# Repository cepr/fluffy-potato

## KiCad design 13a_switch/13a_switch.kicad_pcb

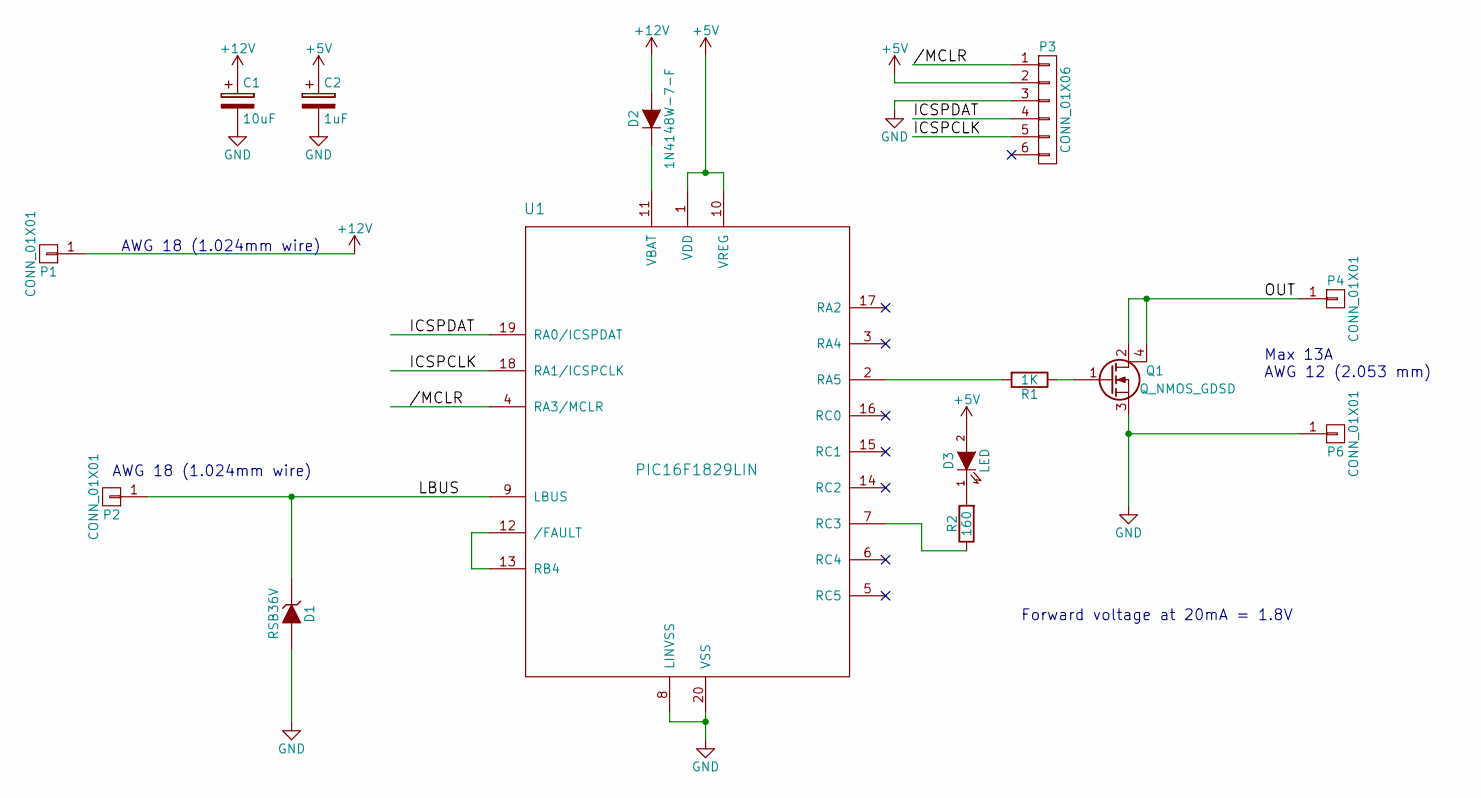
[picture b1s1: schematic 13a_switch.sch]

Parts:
C1: 10uF; C_1210_HandSoldering; DIGIKEY 445-13057-1-ND
C2: 1uF; C_0805_HandSoldering; DIGIKEY 490-8046-1-ND
D1: RSB36V; SOD-323_HandSoldering; DIGIKEY RSB36VTE-17CT-ND
D2: 1N4148W-7-F; SOD-123; DIGIKEY 1N4148W-FDICT-ND
D3: LED; LED_0805; DIGIKEY 475-1415-1-ND
P1, P2, P4, P6: CONN_01X01; 1pin
P3: CONN_01X06; Pin_Header_Straight_1x06
Q1: Q_NMOS_GDSD; SOT-223; DIGIKEY 497-14326-1-ND
R1: 1K; R_0805_HandSoldering; DIGIKEY 311-1.00KCRCT-ND
R2: 160; R_0805_HandSoldering; DIGIKEY 311-160CRCT-ND
U1: PIC16F1829LIN; SSOP-20; DIGIKEY PIC16F1829LIN-I/SS-ND

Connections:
+5V: C2.1, D3.2 (A), P3.2, U1.1 (VDD), U1.10 (VREG)
+12V: C1.1, D2.2 (A), P1.1
//MCLR: P3.1, U1.4 (RA3/MCLR)
/ICSPCLK: P3.5, U1.18 (RA1/ICSPCLK)
/ICSPDAT: P3.4, U1.19 (RA0/ICSPDAT)
/LBUS: D1.1 (K), P2.1, U1.9 (LBUS)
/OUT: P4.1, Q1.2 (D), Q1.4 (D)
GND: C1.2, C2.2, D1.2 (A), P3.3, P6.1, Q1.3 (S), U1.8 (LINVSS), U1.20 (VSS)
unnamed: D2.1 (K), U1.11 (VBAT)
unnamed: D3.1 (K), R2.2
unnamed: Q1.1 (G), R1.1
unnamed: R1.2, U1.2 (RA5)
unnamed: R2.1, U1.7 (RC3)
unnamed: U1.12 (/FAULT), U1.13 (RB4)

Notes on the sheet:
Max 13A AWG 12 (2.053 mm)
AWG 18 (1.024mm wire)
Forward voltage at 20mA = 1.8V

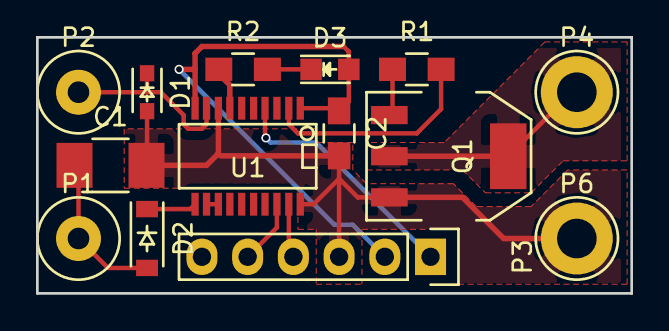
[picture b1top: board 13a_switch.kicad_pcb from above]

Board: 2 copper layers, 33.0 x 14.2 mm, 14 parts (0 on the bottom side), 14 nets.

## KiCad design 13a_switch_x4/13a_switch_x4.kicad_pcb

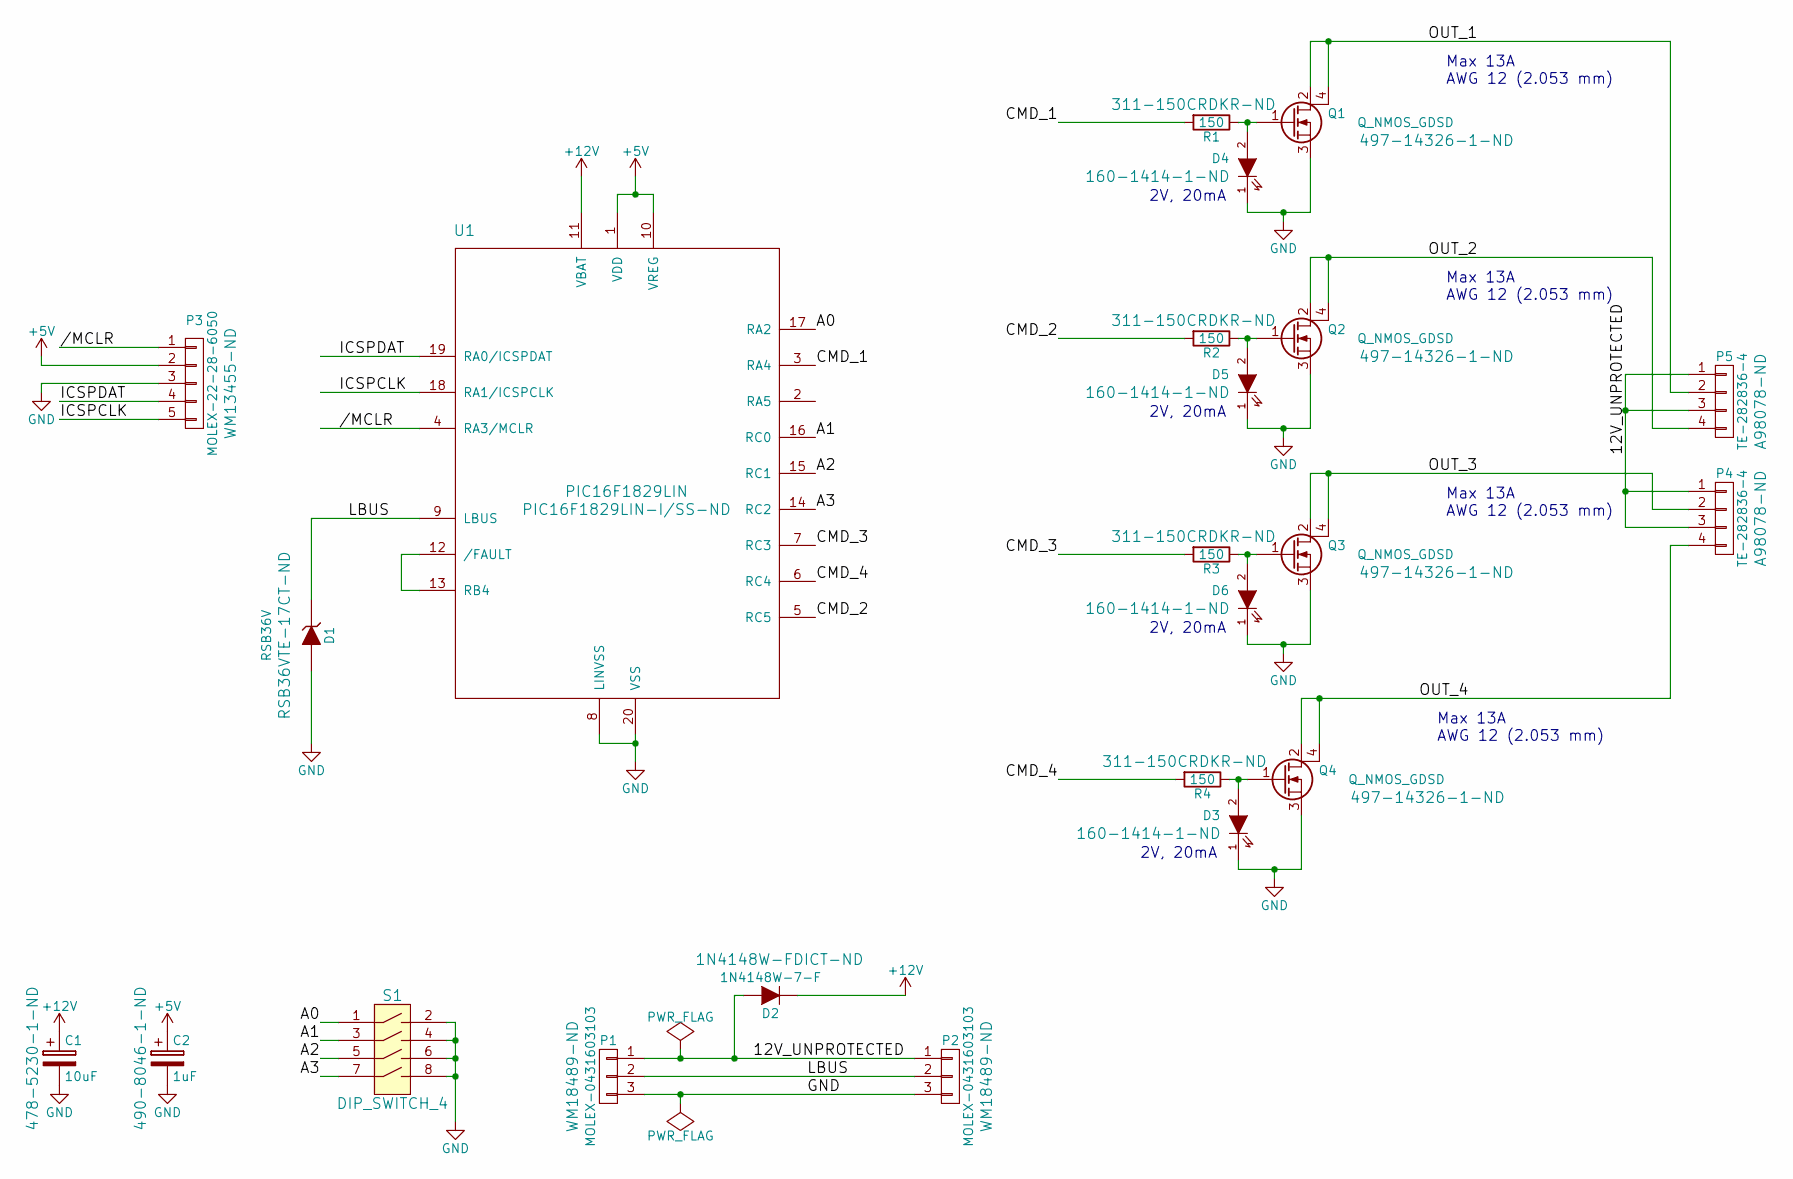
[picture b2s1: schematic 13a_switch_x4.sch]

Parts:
C1: 10uF; C_1210_HandSoldering; DIGIKEY 478-5230-1-ND
C2: 1uF; C_0805_HandSoldering; DIGIKEY 490-8046-1-ND
D1: RSB36V; SOD-323_HandSoldering; DIGIKEY RSB36VTE-17CT-ND
D2: 1N4148W-7-F; SOD-123; DIGIKEY 1N4148W-FDICT-ND
D3, D4, D5, D6: LITEON-LTST-C170KGKT; LED_0805; DIGIKEY 160-1414-1-ND
P1, P2: MOLEX-0431603103; Molex_Sabre_43160-XX03_03x7.49mm_Angled_BoardLock; DIGIKEY WM18489-ND
P3: MOLEX-22-28-6050; Pin_Header_Straight_1x05; DIGIKEY WM13455-ND
P4, P5: TE-282836-4; bornier4; DIGIKEY A98078-ND
Q1, Q2, Q3, Q4: Q_NMOS_GDSD; SOT-223; DIGIKEY 497-14326-1-ND
R1, R2, R3, R4: 150; R_0805_HandSoldering; DIGIKEY 311-150CRDKR-ND
S1: DIP_SWITCH_4; Copal_CHS-04TB; DIGIKEY 563-1008-1-ND
U1: PIC16F1829LIN; SSOP-20_5.3x7.2mm_Pitch0.65mm; DIGIKEY PIC16F1829LIN-I/SS-ND

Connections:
+5V: C2.1, P3.2, U1.1 (VDD), U1.10 (VREG)
+12V: C1.1, D2.1 (K), U1.11 (VBAT)
/12V_UNPROTECTED: D2.2 (A), P1.1, P2.1, P4.1, P4.3, P5.1, P5.3
//MCLR: P3.1, U1.4 (RA3/MCLR)
/A0: S1.1, U1.17 (RA2)
/A1: S1.3, U1.16 (RC0)
/A2: S1.5, U1.15 (RC1)
/A3: S1.7, U1.14 (RC2)
/CMD_1: R1.2, U1.3 (RA4)
/CMD_2: R2.2, U1.5 (RC5)
/CMD_3: R3.2, U1.7 (RC3)
/CMD_4: R4.2, U1.6 (RC4)
/ICSPCLK: P3.5, U1.18 (RA1/ICSPCLK)
/ICSPDAT: P3.4, U1.19 (RA0/ICSPDAT)
/LBUS: D1.1 (K), P1.2, P2.2, U1.9 (LBUS)
/OUT_1: P5.2, Q1.2 (D), Q1.4 (D)
/OUT_2: P5.4, Q2.2 (D), Q2.4 (D)
/OUT_3: P4.2, Q3.2 (D), Q3.4 (D)
/OUT_4: P4.4, Q4.2 (D), Q4.4 (D)
GND: C1.2, C2.2, D1.2 (A), D3.1 (K), D4.1 (K), D5.1 (K), D6.1 (K), P1.3, P2.3, P3.3, Q1.3 (S), Q2.3 (S), Q3.3 (S), Q4.3 (S), S1.2, S1.4, S1.6, S1.8, U1.8 (LINVSS), U1.20 (VSS)
unnamed: D3.2 (A), Q4.1 (G), R4.1
unnamed: D4.2 (A), Q1.1 (G), R1.1
unnamed: D5.2 (A), Q2.1 (G), R2.1
unnamed: D6.2 (A), Q3.1 (G), R3.1
unnamed: U1.12 (/FAULT), U1.13 (RB4)

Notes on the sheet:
Max 13A AWG 12 (2.053 mm)
2V, 20mA

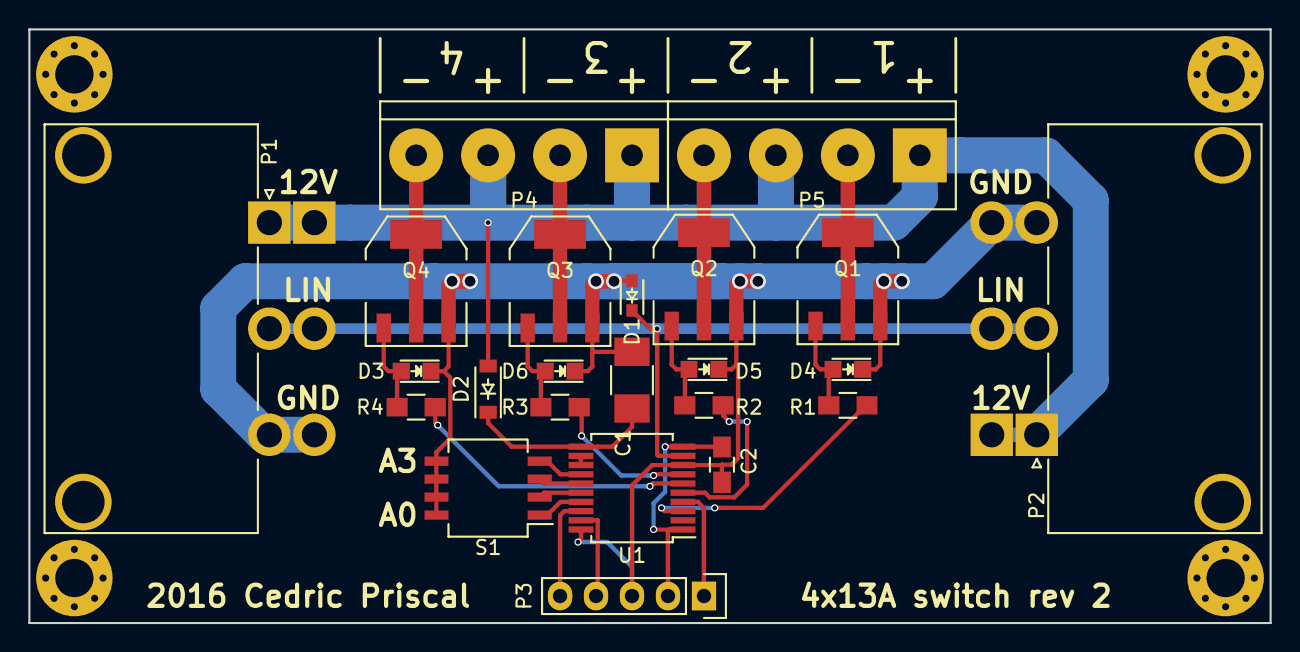
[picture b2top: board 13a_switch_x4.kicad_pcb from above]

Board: 2 copper layers, 87.6 x 41.9 mm, 23 parts (0 on the bottom side), 25 nets.

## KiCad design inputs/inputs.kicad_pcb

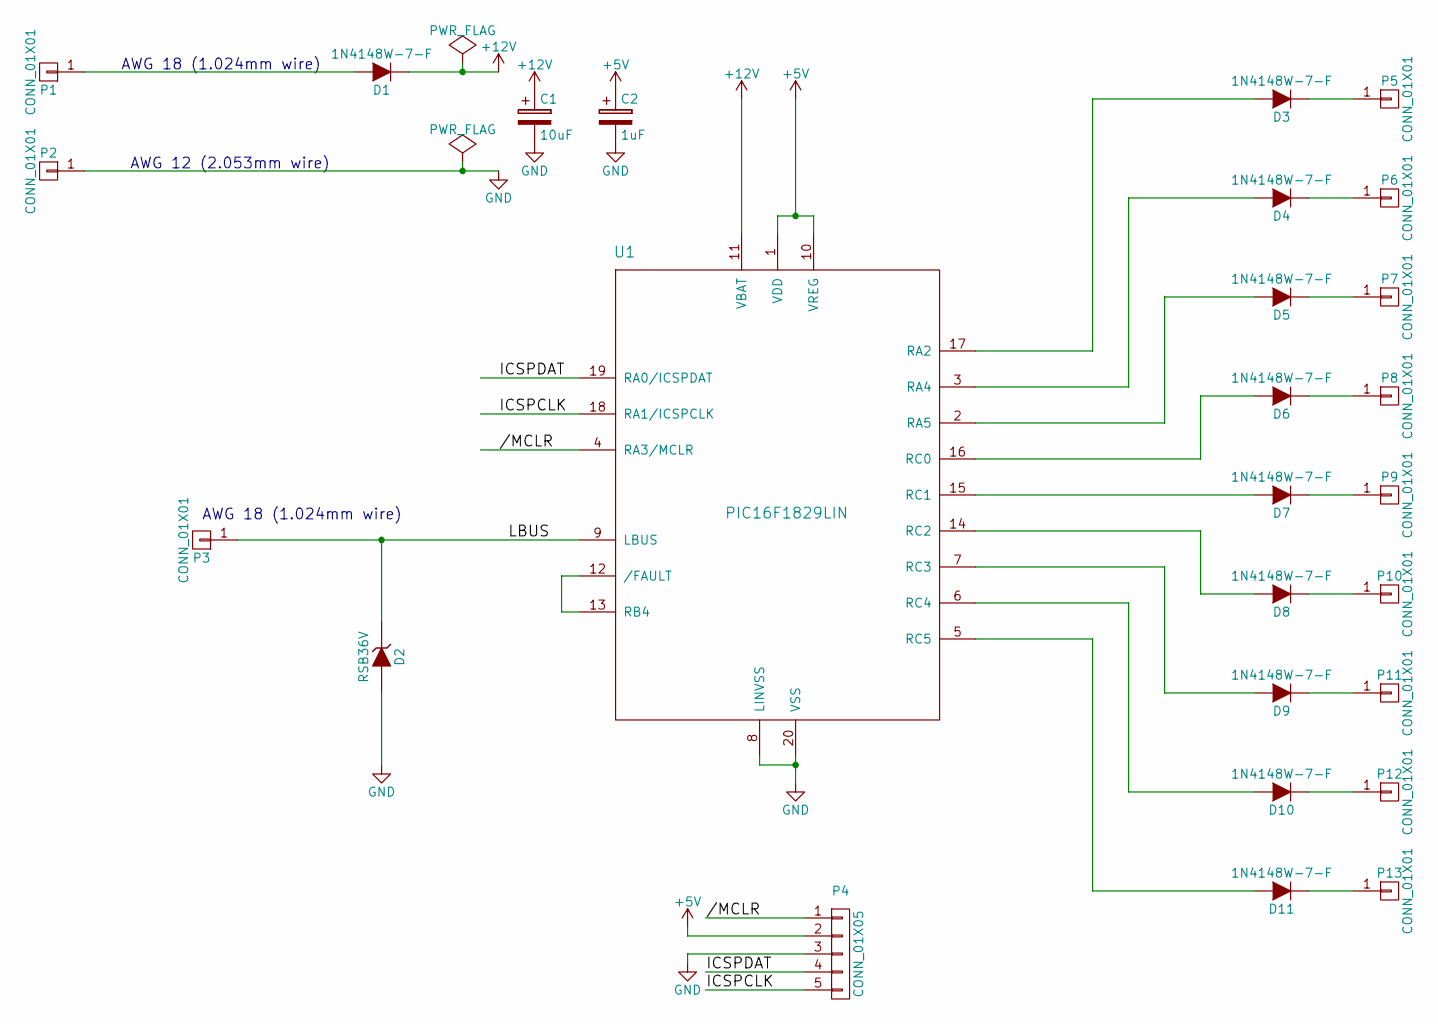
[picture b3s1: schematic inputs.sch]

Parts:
C1: 10uF; C_1210_HandSoldering; DIGIKEY 445-13057-1-ND
C2: 1uF; C_0805_HandSoldering; DIGIKEY 490-8046-1-ND
D1, D3, D4, D5, D6, D7, D8, D9, D10, D11: 1N4148W-7-F; SOD-123; DIGIKEY 1N4148W-FDICT-ND
D2: RSB36V; SOD-323_HandSoldering; DIGIKEY RSB36VTE-17CT-ND
P1, P2, P3, P5, P6, P7, P8, P9, P10, P11, P12, P13: CONN_01X01; wire_awg_18
P4: CONN_01X05; Pin_Header_Angled_1x05
U1: PIC16F1829LIN; SSOP-20_5.3x7.2mm_Pitch0.65mm; DIGIKEY PIC16F1829LIN-I/SS-ND

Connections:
+5V: C2.1, P4.2, U1.1 (VDD), U1.10 (VREG)
+12V: C1.1, D1.1 (K), U1.11 (VBAT)
//MCLR: P4.1, U1.4 (RA3/MCLR)
/ICSPCLK: P4.5, U1.18 (RA1/ICSPCLK)
/ICSPDAT: P4.4, U1.19 (RA0/ICSPDAT)
/LBUS: D2.1 (K), P3.1, U1.9 (LBUS)
GND: C1.2, C2.2, D2.2 (A), P2.1, P4.3, U1.8 (LINVSS), U1.20 (VSS)
unnamed: D1.2 (A), P1.1
unnamed: D3.1 (K), P5.1
unnamed: D3.2 (A), U1.17 (RA2)
unnamed: D4.1 (K), P6.1
unnamed: D4.2 (A), U1.3 (RA4)
unnamed: D5.1 (K), P7.1
unnamed: D5.2 (A), U1.2 (RA5)
unnamed: D6.1 (K), P8.1
unnamed: D6.2 (A), U1.16 (RC0)
unnamed: D7.1 (K), P9.1
unnamed: D7.2 (A), U1.15 (RC1)
unnamed: D8.1 (K), P10.1
unnamed: D8.2 (A), U1.14 (RC2)
unnamed: D9.1 (K), P11.1
unnamed: D9.2 (A), U1.7 (RC3)
unnamed: D10.1 (K), P12.1
unnamed: D10.2 (A), U1.6 (RC4)
unnamed: D11.1 (K), P13.1
unnamed: D11.2 (A), U1.5 (RC5)
unnamed: U1.12 (/FAULT), U1.13 (RB4)

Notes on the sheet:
AWG 18 (1.024mm wire)
AWG 12 (2.053mm wire)

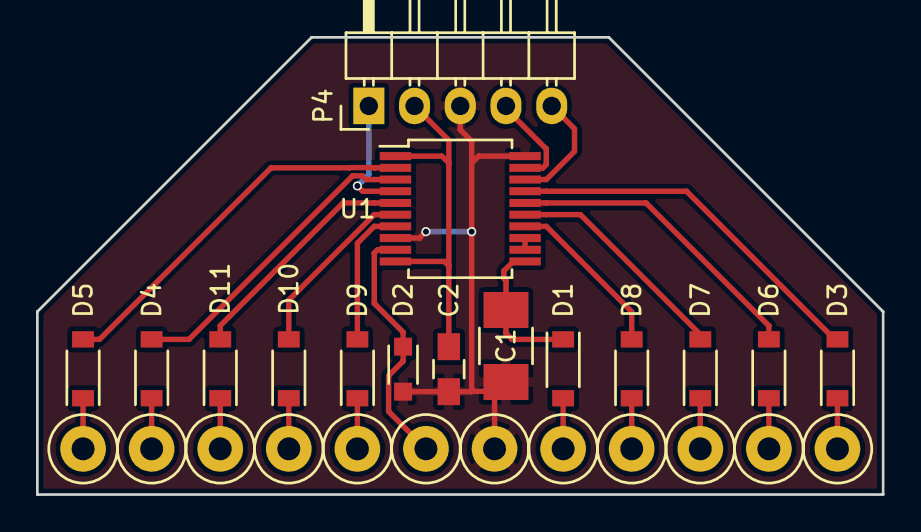
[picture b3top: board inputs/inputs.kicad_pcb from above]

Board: 2 copper layers, 47.0 x 25.4 mm, 27 parts (0 on the bottom side), 27 nets.

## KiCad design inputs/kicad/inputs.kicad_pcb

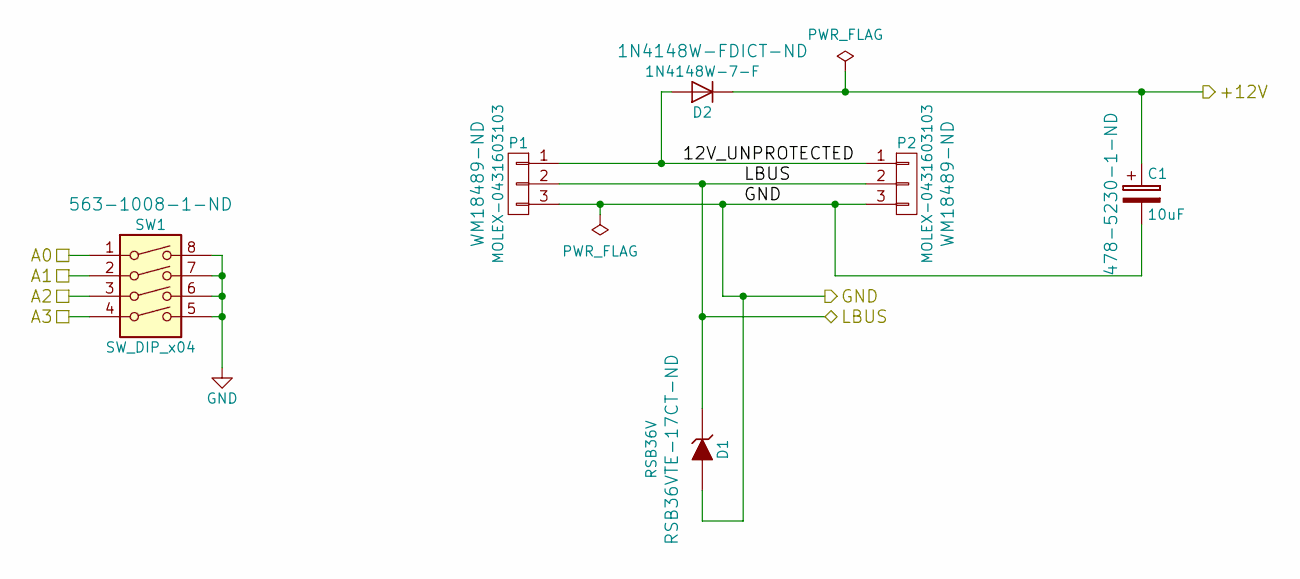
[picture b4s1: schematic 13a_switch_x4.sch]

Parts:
C1: 10uF; C_1210_HandSoldering; DIGIKEY 478-5230-1-ND
D1: RSB36V; SOD-323_HandSoldering; DIGIKEY RSB36VTE-17CT-ND
D2: 1N4148W-7-F; SOD-123; DIGIKEY 1N4148W-FDICT-ND
P1, P2: MOLEX-0431603103; Molex_Sabre_43160-XX03_03x7.49mm_Angled_BoardLock; DIGIKEY WM18489-ND
SW1: SW_DIP_x04; SW_DIP_x4_W7.62mm_Slide_Copal_CHS-B; DIGIKEY 563-1008-1-ND

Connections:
/Sheet584DA639/+12V: C1.1, D2.1 (K); also elsewhere on the board
/Sheet584DA639/LBUS: D1.1 (K), P1.2, P2.2; also elsewhere on the board
/lin_common/12V_UNPROTECTED: D2.2 (A), P1.1, P2.1
/lin_common/A0: SW1.1; also elsewhere on the board
/lin_common/A1: SW1.2; also elsewhere on the board
/lin_common/A2: SW1.3; also elsewhere on the board
/lin_common/A3: SW1.4; also elsewhere on the board
GND: C1.2, D1.2 (A), P1.3, P2.3, SW1.5, SW1.6, SW1.7, SW1.8; also elsewhere on the board

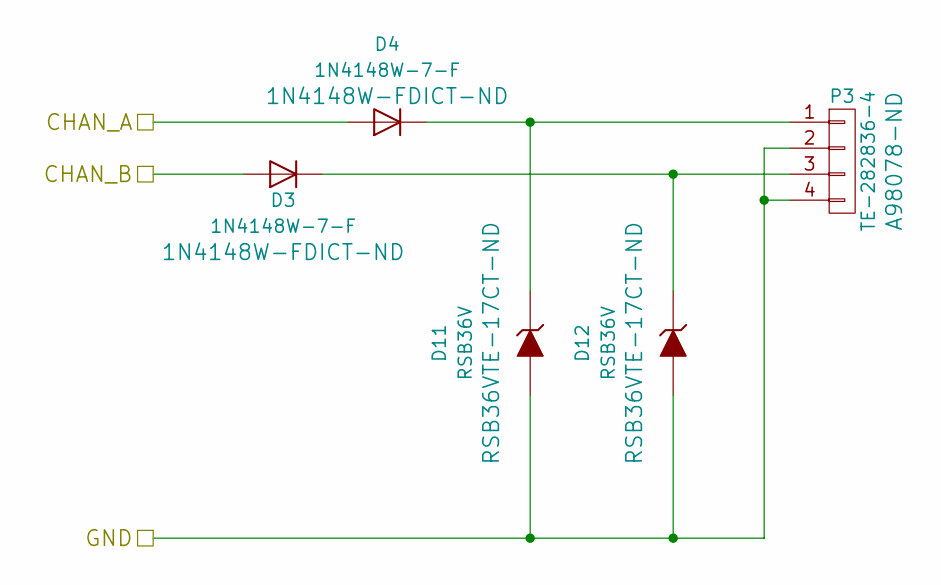
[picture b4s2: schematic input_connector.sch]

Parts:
D3, D4: 1N4148W-7-F; SOD-123; DIGIKEY 1N4148W-FDICT-ND
D11, D12: RSB36V; SOD-323_HandSoldering; DIGIKEY RSB36VTE-17CT-ND
P3: TE-282836-4; bornier4; DIGIKEY A98078-ND

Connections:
/IN0: D4.2 (A); also elsewhere on the board
/IN1: D3.2 (A); also elsewhere on the board
GND: D11.2 (A), D12.2 (A), P3.2, P3.4; also elsewhere on the board
unnamed: D4.1 (K), D11.1 (K), P3.1
unnamed: D3.1 (K), D12.1 (K), P3.3

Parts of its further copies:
D5, D6, D7, D8, D9, D10: 1N4148W-7-F; SOD-123; DIGIKEY 1N4148W-FDICT-ND
D13, D14, D15, D16, D17, D18: RSB36V; SOD-323_HandSoldering; DIGIKEY RSB36VTE-17CT-ND
P4, P5, P6: TE-282836-4; bornier4; DIGIKEY A98078-ND

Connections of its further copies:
/IN2: D8.2 (A); also elsewhere on the board
/IN3: D7.2 (A); also elsewhere on the board
/IN4: D6.2 (A); also elsewhere on the board
/IN5: D5.2 (A); also elsewhere on the board
/IN6: D10.2 (A); also elsewhere on the board
/IN7: D9.2 (A); also elsewhere on the board
GND: D13.2 (A), D14.2 (A), D15.2 (A), D16.2 (A), D17.2 (A), D18.2 (A), P4.2, P4.4, P5.2, P5.4, P6.2, P6.4; also elsewhere on the board
unnamed: D10.1 (K), D17.1 (K), P6.1
unnamed: D6.1 (K), D13.1 (K), P4.1
unnamed: D5.1 (K), D14.1 (K), P4.3
unnamed: D8.1 (K), D15.1 (K), P5.1
unnamed: D7.1 (K), D16.1 (K), P5.3
unnamed: D9.1 (K), D18.1 (K), P6.3

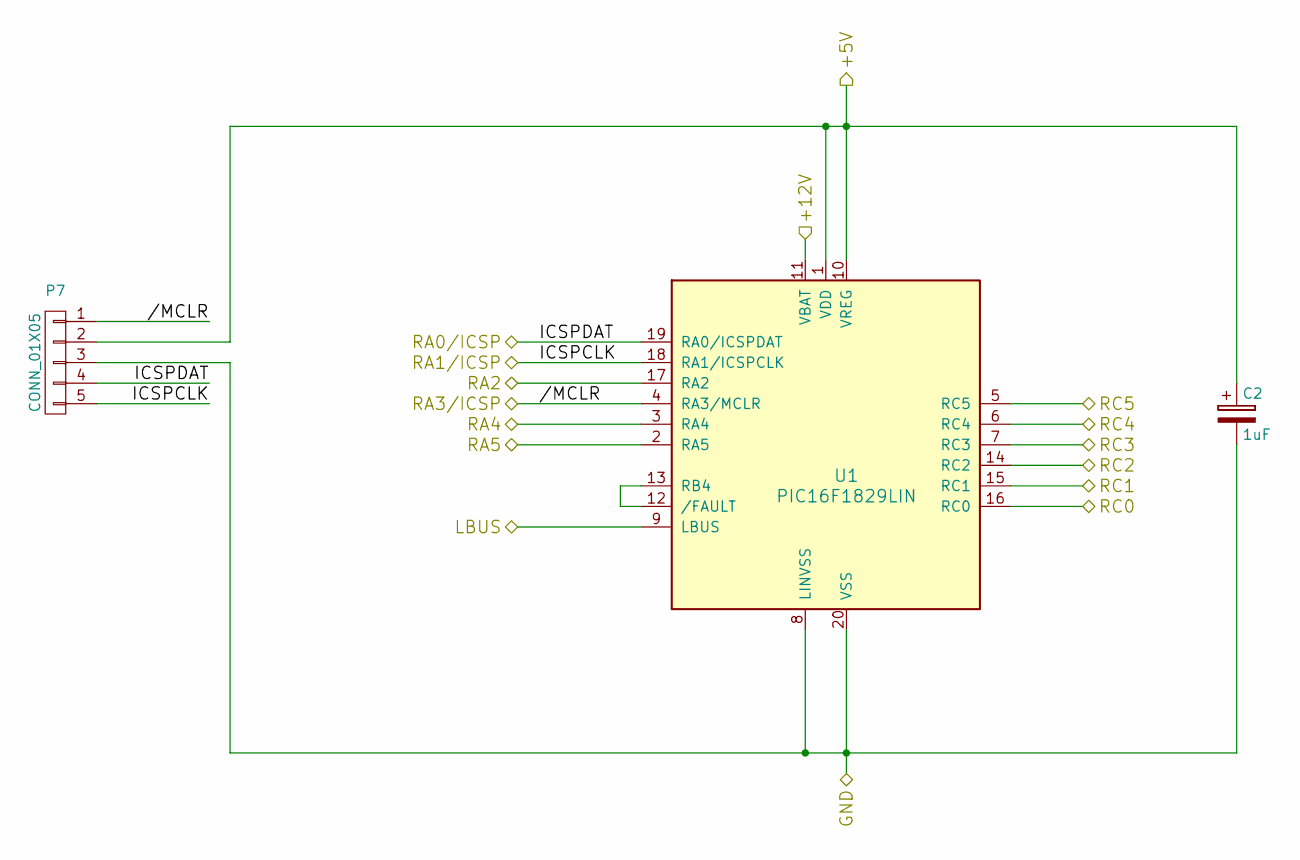
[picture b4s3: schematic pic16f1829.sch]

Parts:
C2: 1uF; C_0805_HandSoldering; DIGIKEY 490-8046-1-ND
P7: CONN_01X05; Pin_Header_Angled_1x05
U1: PIC16F1829LIN; SSOP-20_5.3x7.2mm_Pitch0.65mm; DIGIKEY PIC16F1829LIN-I/SS-ND

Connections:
/IN0: U1.14 (RC2); also elsewhere on the board
/IN1: U1.15 (RC1); also elsewhere on the board
/IN2: U1.16 (RC0); also elsewhere on the board
/IN3: U1.17 (RA2); also elsewhere on the board
/IN4: U1.2 (RA5); also elsewhere on the board
/IN5: U1.3 (RA4); also elsewhere on the board
/IN6: U1.6 (RC4); also elsewhere on the board
/IN7: U1.7 (RC3); also elsewhere on the board
/Sheet584DA639/+5V: C2.1, P7.2, U1.1 (VDD), U1.10 (VREG)
/Sheet584DA639/+12V: U1.11 (VBAT); also elsewhere on the board
/Sheet584DA639/LBUS: U1.9 (LBUS); also elsewhere on the board
/lin_common/A0: P7.5, U1.18 (RA1/ICSPCLK); also elsewhere on the board
/lin_common/A1: P7.4, U1.19 (RA0/ICSPDAT); also elsewhere on the board
/lin_common/A2: P7.1, U1.4 (RA3/MCLR); also elsewhere on the board
/lin_common/A3: U1.5 (RC5); also elsewhere on the board
GND: C2.2, P7.3, U1.8 (LINVSS), U1.20 (VSS); also elsewhere on the board
unnamed: U1.12 (/FAULT), U1.13 (RB4)

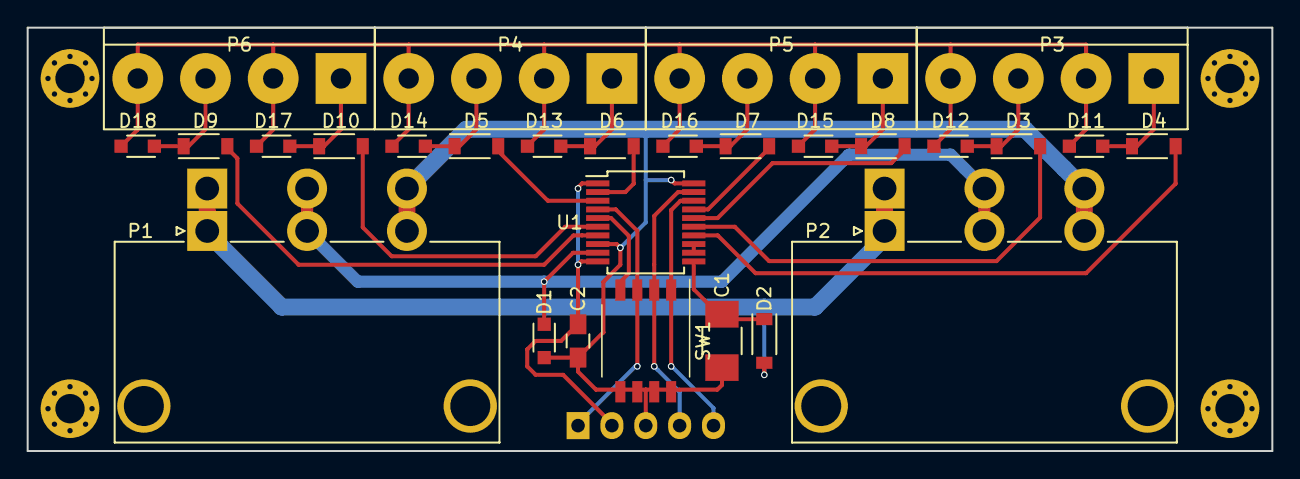
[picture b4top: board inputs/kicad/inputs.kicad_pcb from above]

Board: 2 copper layers, 93.3 x 31.7 mm, 29 parts (1 on the bottom side), 26 nets.

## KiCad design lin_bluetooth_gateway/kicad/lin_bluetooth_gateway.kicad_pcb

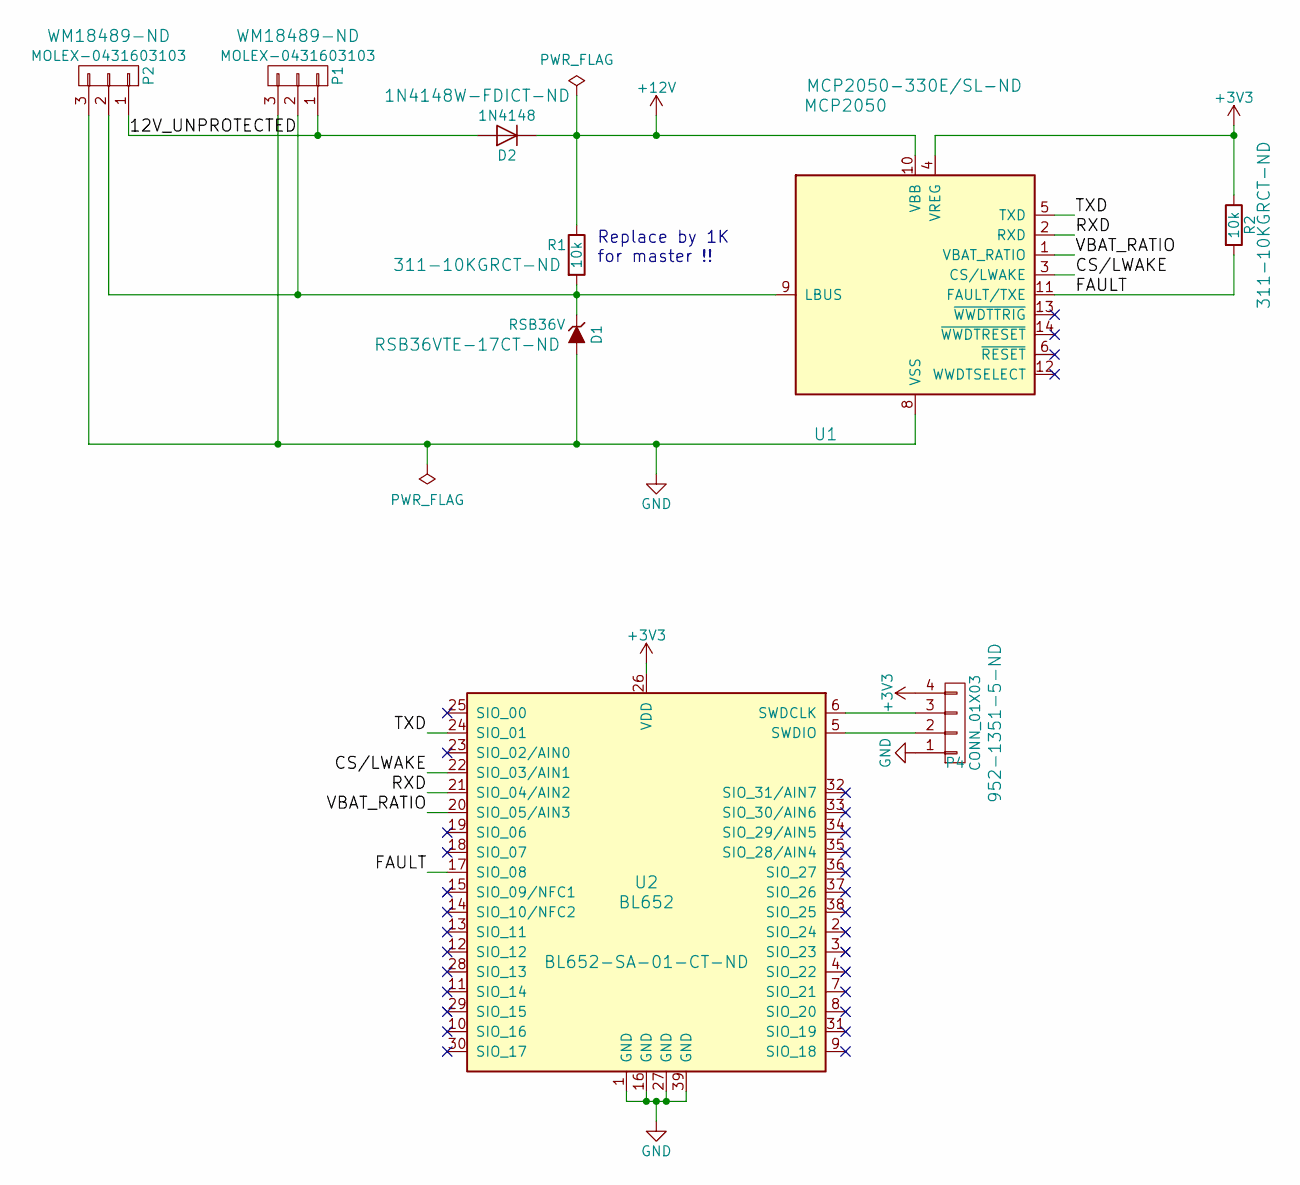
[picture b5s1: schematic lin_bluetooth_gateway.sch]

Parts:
D1: RSB36V; SOD-323_HandSoldering; DIGIKEY RSB36VTE-17CT-ND
D2: 1N4148; SOD-123; DIGIKEY 1N4148W-FDICT-ND
P1, P2: MOLEX-0431603103; Molex_Sabre_43160-XX03_03x7.49mm_Angled_BoardLock; DIGIKEY WM18489-ND
P4: CONN_01X03; Pin_Header_Straight_1x04_Pitch2.00mm; DIGIKEY 952-1351-5-ND
R1, R2: 10k; R_0603_HandSoldering; DIGIKEY 311-10KGRCT-ND
U1: MCP2050; SOIC-14_3.9x8.7mm_Pitch1.27mm; DIGIKEY MCP2050-330E/SL-ND
U2: BL652; Laird_BL652; DIGIKEY BL652-SA-01-CT-ND

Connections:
+3V3: P4.4, R2.1, U1.4 (VREG), U2.26 (VDD)
+12V: D2.1 (K), R1.1, U1.10 (VBB)
/12V_UNPROTECTED: D2.2 (A), P1.1, P2.1
/CS/LWAKE: U1.3 (CS/LWAKE), U2.22 (SIO_03/AIN1)
/FAULT: R2.2, U1.11 (FAULT/TXE), U2.17 (SIO_08)
/RXD: U1.2 (RXD), U2.21 (SIO_04/AIN2)
/TXD: U1.5 (TXD), U2.24 (SIO_01)
/VBAT_RATIO: U1.1 (VBAT_RATIO), U2.20 (SIO_05/AIN3)
GND: D1.2 (A), P1.3, P2.3, P4.1, U1.8 (VSS), U2.1 (GND), U2.16 (GND), U2.27 (GND), U2.39 (GND)
unnamed: D1.1 (K), P1.2, P2.2, R1.2, U1.9 (LBUS)
unnamed: P4.2, U2.5 (SWDIO)
unnamed: P4.3, U2.6 (SWDCLK)

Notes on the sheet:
Replace by 1K for master !!

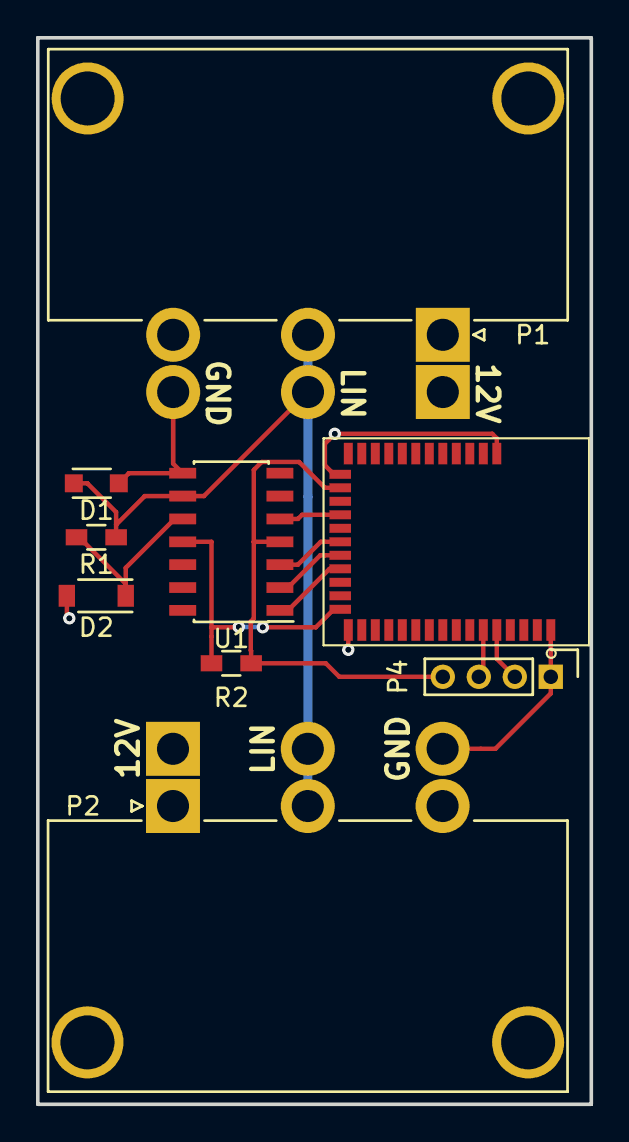
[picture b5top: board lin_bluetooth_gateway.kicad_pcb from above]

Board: 2 copper layers, 30.8 x 59.2 mm, 9 parts (0 on the bottom side), 12 nets.
